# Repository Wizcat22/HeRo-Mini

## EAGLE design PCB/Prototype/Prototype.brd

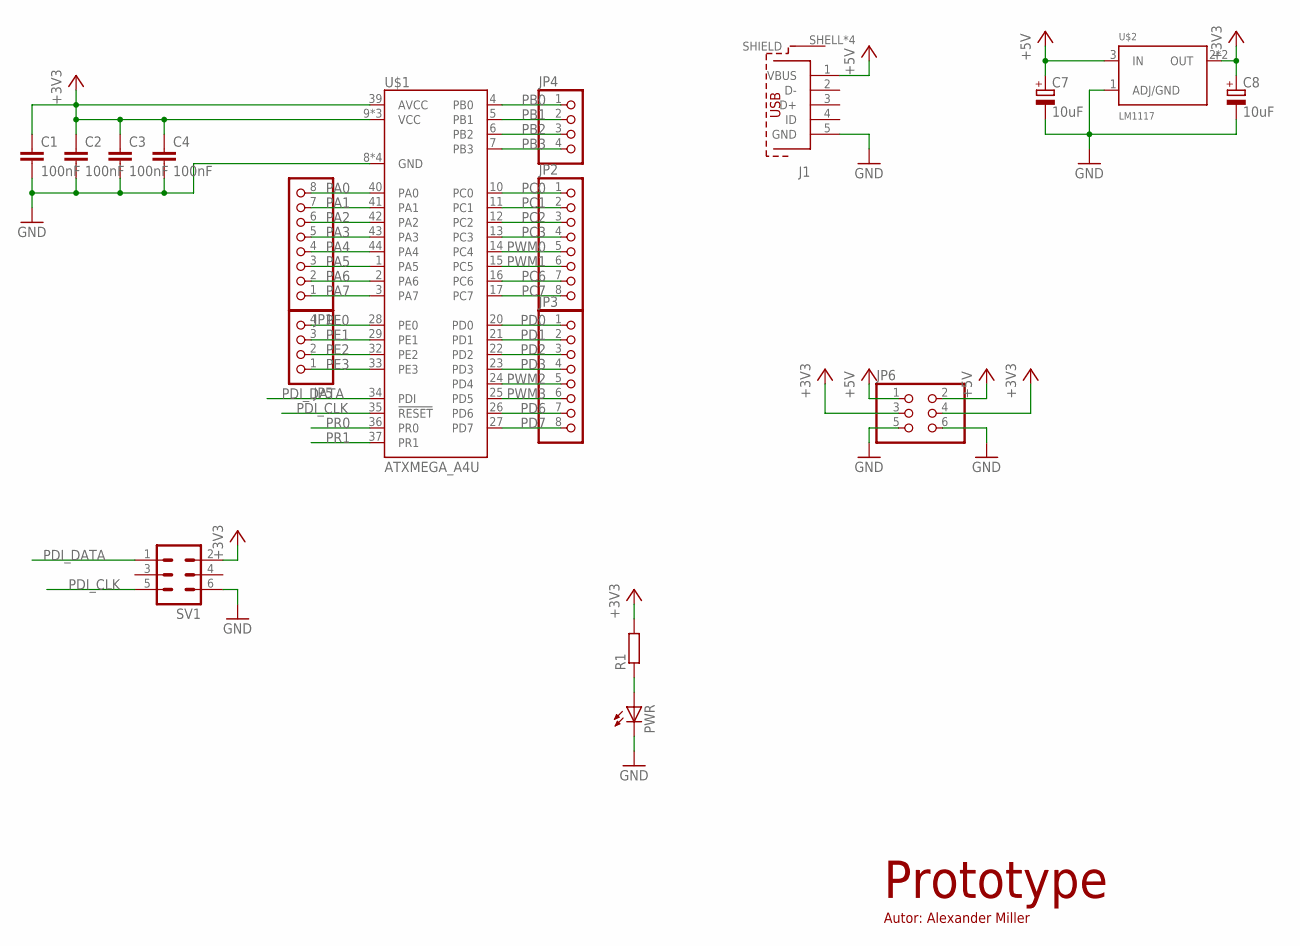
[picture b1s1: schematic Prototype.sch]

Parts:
C1, C2, C3, C4: 100nF; C0805
C7, C8: 10uF; SMC_P
J1: 629105136821
JP1, JP2, JP3: PINHD-1X8; 1X08
JP4, JP5: PINHD-1X4; 1X04
JP6: PINHD-2X3; 2X03
PWR: LEDSML0805; SML0805
R1: R-EU_R0805; R0805
SV1: ML6
U$1: ATXMEGA_A4U; QFP80P1200X1200X120-44
U$2: LM1117; SOT223

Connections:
+3V3: C1.1, C2.1, C3.1, C4.1, C8.+, JP6.3, JP6.4, R1.2, SV1.2, U$1.9 (VCC), U$1.19 (VCC), U$1.31 (VCC), U$1.39 (AVCC), U$2.2 (OUT), U$2.4 (OUT)
+5V: C7.+, J1.1 (VBUS), JP6.1, JP6.2, U$2.3 (IN)
GND: C1.2, C2.2, C3.2, C4.2, C7.-, C8.-, J1.5 (GND), JP6.5, JP6.6, PWR.C, SV1.6, U$1.8 (GND), U$1.18 (GND), U$1.30 (GND), U$1.38 (GND), U$2.1 (ADJ/GND)
unnamed: PWR.A, R1.1
PA0: JP1.8, U$1.40 (PA0)
PA1: JP1.7, U$1.41 (PA1)
PA2: JP1.6, U$1.42 (PA2)
PA3: JP1.5, U$1.43 (PA3)
PA4: JP1.4, U$1.44 (PA4)
PA5: JP1.3, U$1.1 (PA5)
PA6: JP1.2, U$1.2 (PA6)
PA7: JP1.1, U$1.3 (PA7)
PB0: JP4.1, U$1.4 (PB0)
PB1: JP4.2, U$1.5 (PB1)
PB2: JP4.3, U$1.6 (PB2)
PB3: JP4.4, U$1.7 (PB3)
PC0: JP2.1, U$1.10 (PC0)
PC1: JP2.2, U$1.11 (PC1)
PC2: JP2.3, U$1.12 (PC2)
PC3: JP2.4, U$1.13 (PC3)
PC6: JP2.7, U$1.16 (PC6)
PC7: JP2.8, U$1.17 (PC7)
PD0: JP3.1, U$1.20 (PD0)
PD1: JP3.2, U$1.21 (PD1)
PD2: JP3.3, U$1.22 (PD2)
PD3: JP3.4, U$1.23 (PD3)
PD6: JP3.7, U$1.26 (PD6)
PD7: JP3.8, U$1.27 (PD7)
PDI_CLK: SV1.5, U$1.35 (!RESET)
PDI_DATA: SV1.1, U$1.34 (PDI)
PE0: JP5.4, U$1.28 (PE0)
PE1: JP5.3, U$1.29 (PE1)
PE2: JP5.2, U$1.32 (PE2)
PE3: JP5.1, U$1.33 (PE3)
PR0: U$1.36 (PR0)
PR1: U$1.37 (PR1)
PWM0: JP2.5, U$1.14 (PC4)
PWM1: JP2.6, U$1.15 (PC5)
PWM2: JP3.5, U$1.24 (PD4)
PWM3: JP3.6, U$1.25 (PD5)

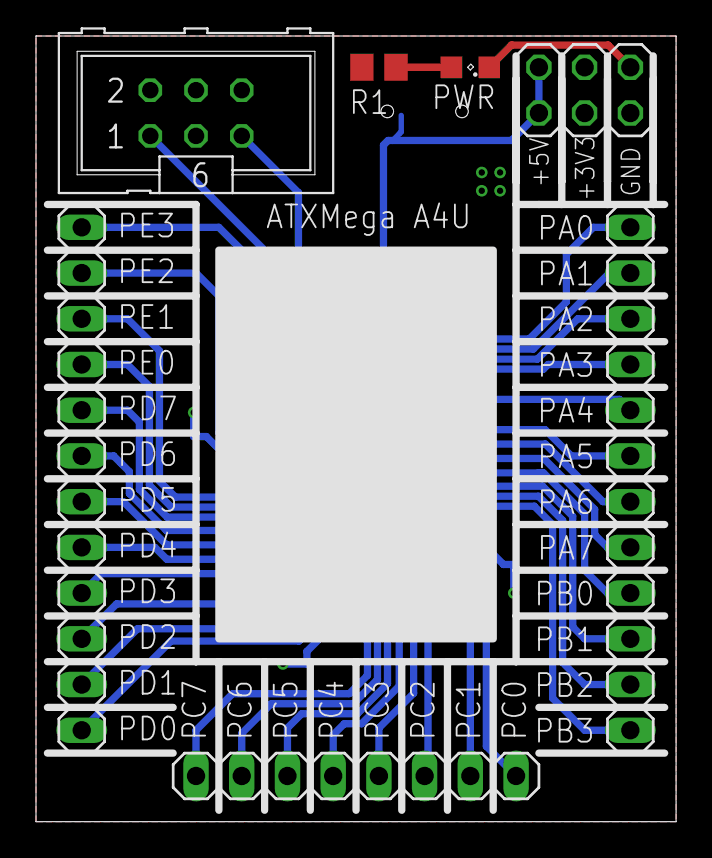
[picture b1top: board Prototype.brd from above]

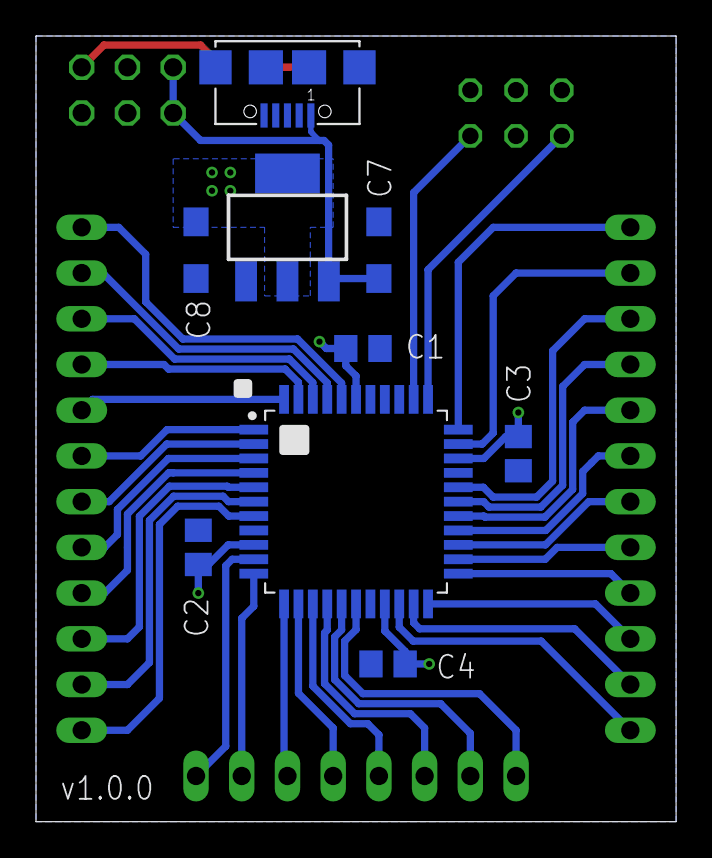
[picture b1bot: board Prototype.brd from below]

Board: 2 copper layers, 35.6 x 43.6 mm, 18 parts (9 on the bottom side), 38 nets.

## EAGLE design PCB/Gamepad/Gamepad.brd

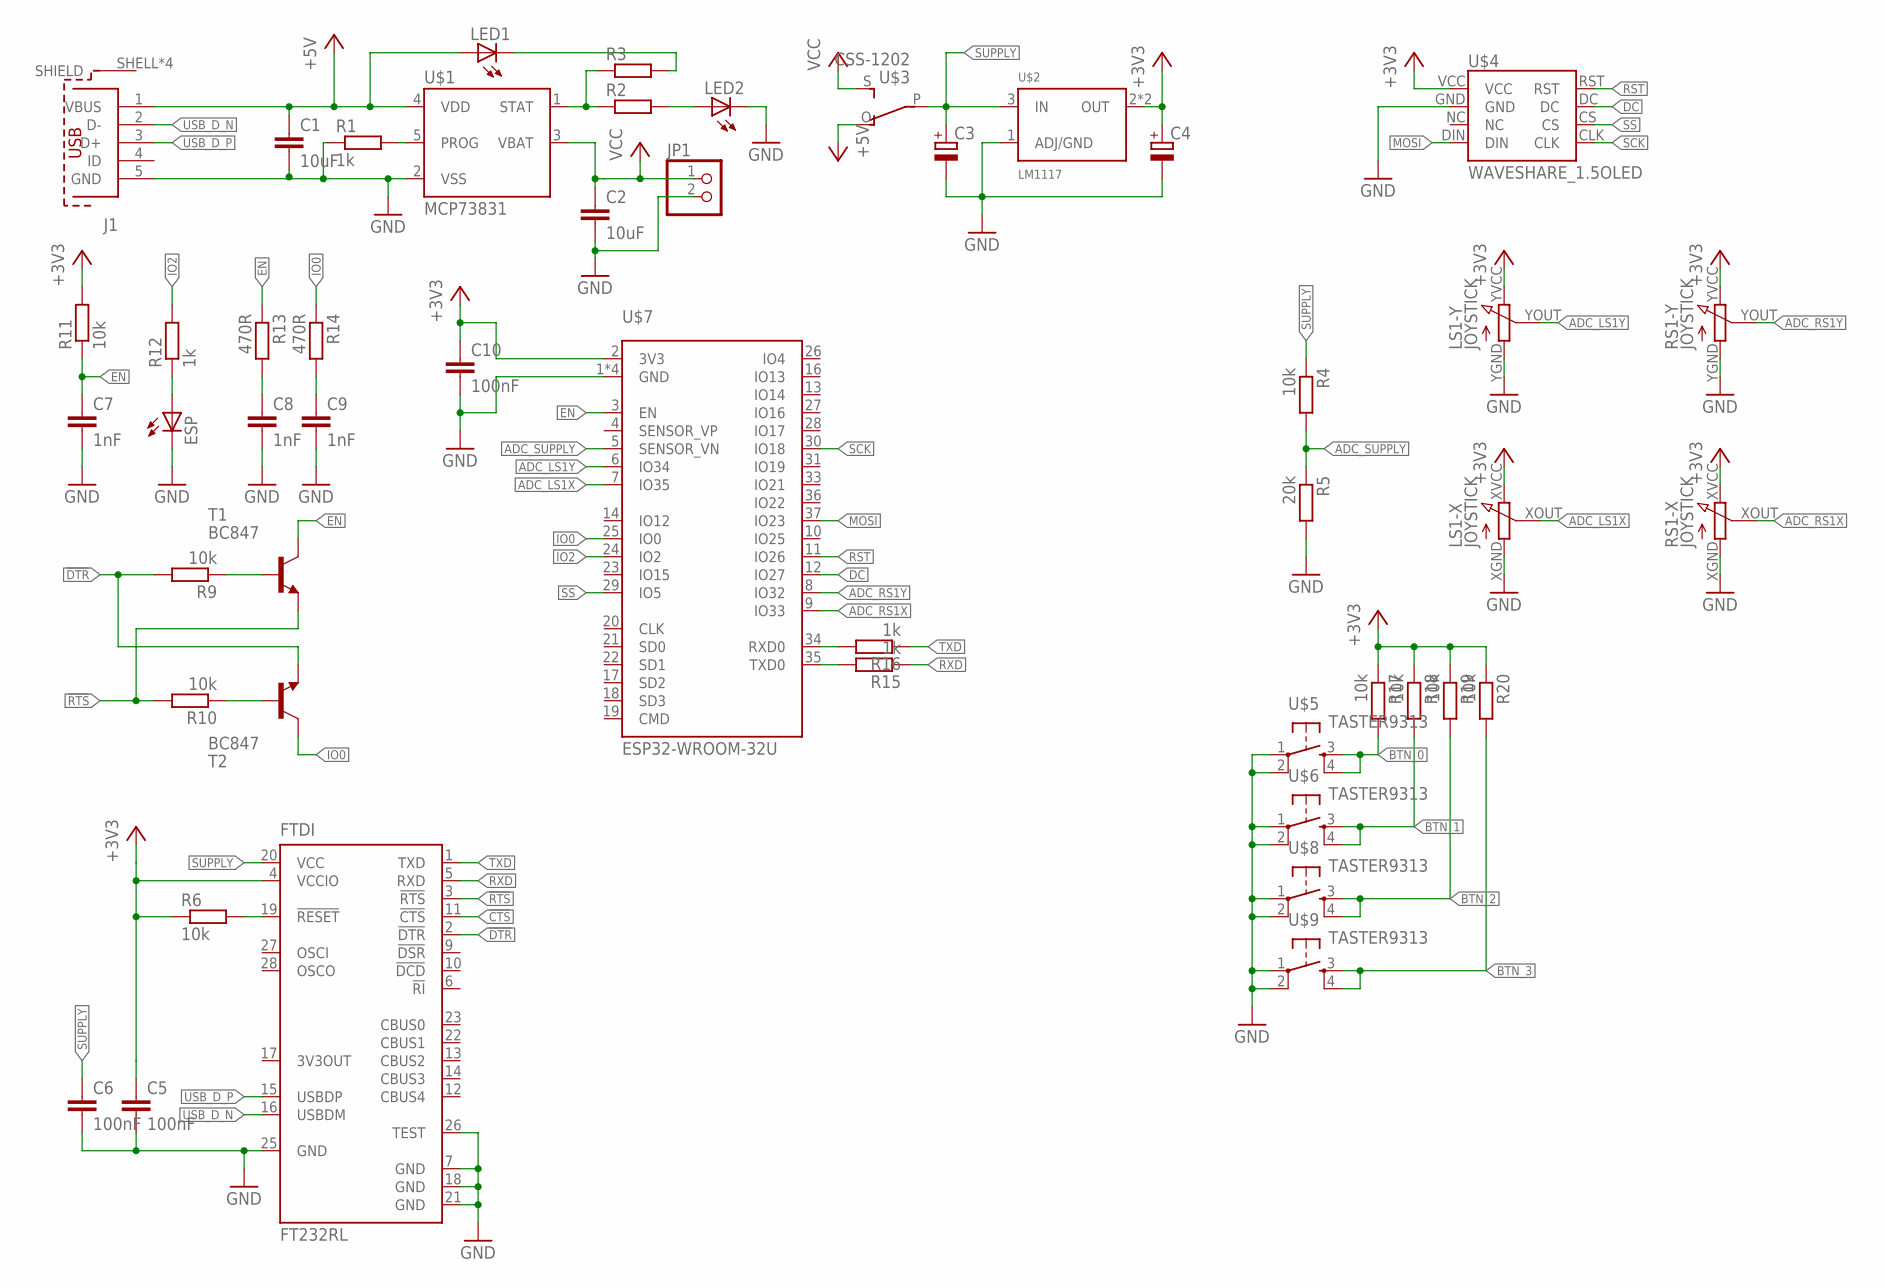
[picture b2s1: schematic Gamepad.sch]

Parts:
C1, C2: 10uF; C0805
C3, C4: CPOL-EUSMCP; SMC_P
C5, C6, C10: 100nF; C0805
C7, C8, C9: 1nF; C0805
ESP: LEDCHIP-LED0805; CHIP-LED0805
FTDI: FT232RL; SSOP28
J1: 629105136821
JP1: PINHD-1X2; 1X02
LED1, LED2: LED3MM
LS1: JOYSTICK
R1, R12, R15, R16: 1k; R0805
R2, R3: R-EU_R0805; R0805
R4, R6, R9, R10, R11, R17, R18, R19, R20: 10k; R0805
R5: 20k; R0805
R13, R14: 470R; R0805
RS1: JOYSTICK
T1, T2: BC847; SOT23
U$1: MCP73831; SOT95P280X145-5
U$2: LM1117; SOT223
U$3: CSS-1202
U$4: WAVESHARE_1.5OLED
U$5, U$6, U$8, U$9: TASTER9313
U$7: ESP32-WROOM-32U

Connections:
!CTS: FTDI.11 (!CTS)
!DTR: FTDI.2 (!DTR), R9.2, T2.2 (E)
!RTS: FTDI.3 (!RTS), R10.2, T1.2 (E)
+3V3: C4.+, C5.1, C10.1, FTDI.4 (VCCIO), LS1.XVCC (VCC), LS1.YVCC (VCC), R6.1, R11.2, R17.1, R18.1, R19.1, R20.1, RS1.XVCC (VCC), RS1.YVCC (VCC), U$2.2 (OUT), U$2.4 (OUT), U$4.VCC, U$7.2 (3V3)
+5V: C1.1, J1.1 (VBUS), LED1.A, U$1.4 (VDD), U$3.O
ADC_LS1X: LS1.XOUT (OUT), U$7.7 (IO35)
ADC_LS1Y: LS1.YOUT (OUT), U$7.6 (IO34)
ADC_RS1X: RS1.XOUT (OUT), U$7.9 (IO33)
ADC_RS1Y: RS1.YOUT (OUT), U$7.8 (IO32)
ADC_SUPPLY: R4.2, R5.1, U$7.5 (SENSOR_VN)
BTN_0: R17.2, U$5.3 (S), U$5.4 (S1)
BTN_1: R18.2, U$6.3 (S), U$6.4 (S1)
BTN_2: R19.2, U$8.3 (S), U$8.4 (S1)
BTN_3: R20.2, U$9.3 (S), U$9.4 (S1)
DC: U$4.DC, U$7.12 (IO27)
EN: C7.1, R11.1, R13.1, T1.3 (C), U$7.3 (EN)
GND: C1.2, C2.2, C3.-, C4.-, C5.2, C6.2, C7.2, C8.2, C9.2, C10.2, ESP.C, FTDI.7 (GND), FTDI.18 (GND), FTDI.21 (GND), FTDI.25 (GND), FTDI.26 (TEST), J1.5 (GND), JP1.2, LED2.K (C), LS1.XGND (GND), LS1.YGND (GND), R1.1, R5.2, RS1.XGND (GND), RS1.YGND (GND), U$1.2 (VSS), U$2.1 (ADJ/GND), U$4.GND, U$5.1, U$5.2 (P1), U$6.1, U$6.2 (P1), U$7.1 (GND), U$7.15 (GND), U$7.38 (GND), U$7.39 (GND), U$8.1, U$8.2 (P1), U$9.1, U$9.2 (P1)
IO0: R14.1, T2.3 (C), U$7.25 (IO0)
IO2: R12.2, U$7.24 (IO2)
MOSI: U$4.DIN, U$7.37 (IO23)
unnamed: R2.1, R3.1, U$1.1 (STAT)
unnamed: FTDI.19 (!RESET), R6.2
unnamed: R1.2, U$1.5 (PROG)
unnamed: LED1.K (C), R3.2
unnamed: LED2.A, R2.2
unnamed: R9.1, T1.1 (B)
unnamed: R10.1, T2.1 (B)
unnamed: ESP.A, R12.1
unnamed: C8.1, R13.2
unnamed: C9.1, R14.2
unnamed: R16.2, U$7.34 (RXD0)
unnamed: R15.2, U$7.35 (TXD0)
RST: U$4.RST, U$7.11 (IO26)
RXD: FTDI.5 (RXD), R15.1
SCK: U$4.CLK, U$7.30 (IO18)
SS: U$4.CS, U$7.29 (IO5)
SUPPLY: C3.+, C6.1, FTDI.20 (VCC), R4.1, U$2.3 (IN), U$3.P
TXD: FTDI.1 (TXD), R16.1
USB_D_N: FTDI.16 (USBDM), J1.2 (D-)
USB_D_P: FTDI.15 (USBDP), J1.3 (D+)
VCC: C2.1, JP1.1, U$1.3 (VBAT), U$3.S

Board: 2 copper layers, 47 parts (31 on the bottom side), 40 nets, no tracks yet.

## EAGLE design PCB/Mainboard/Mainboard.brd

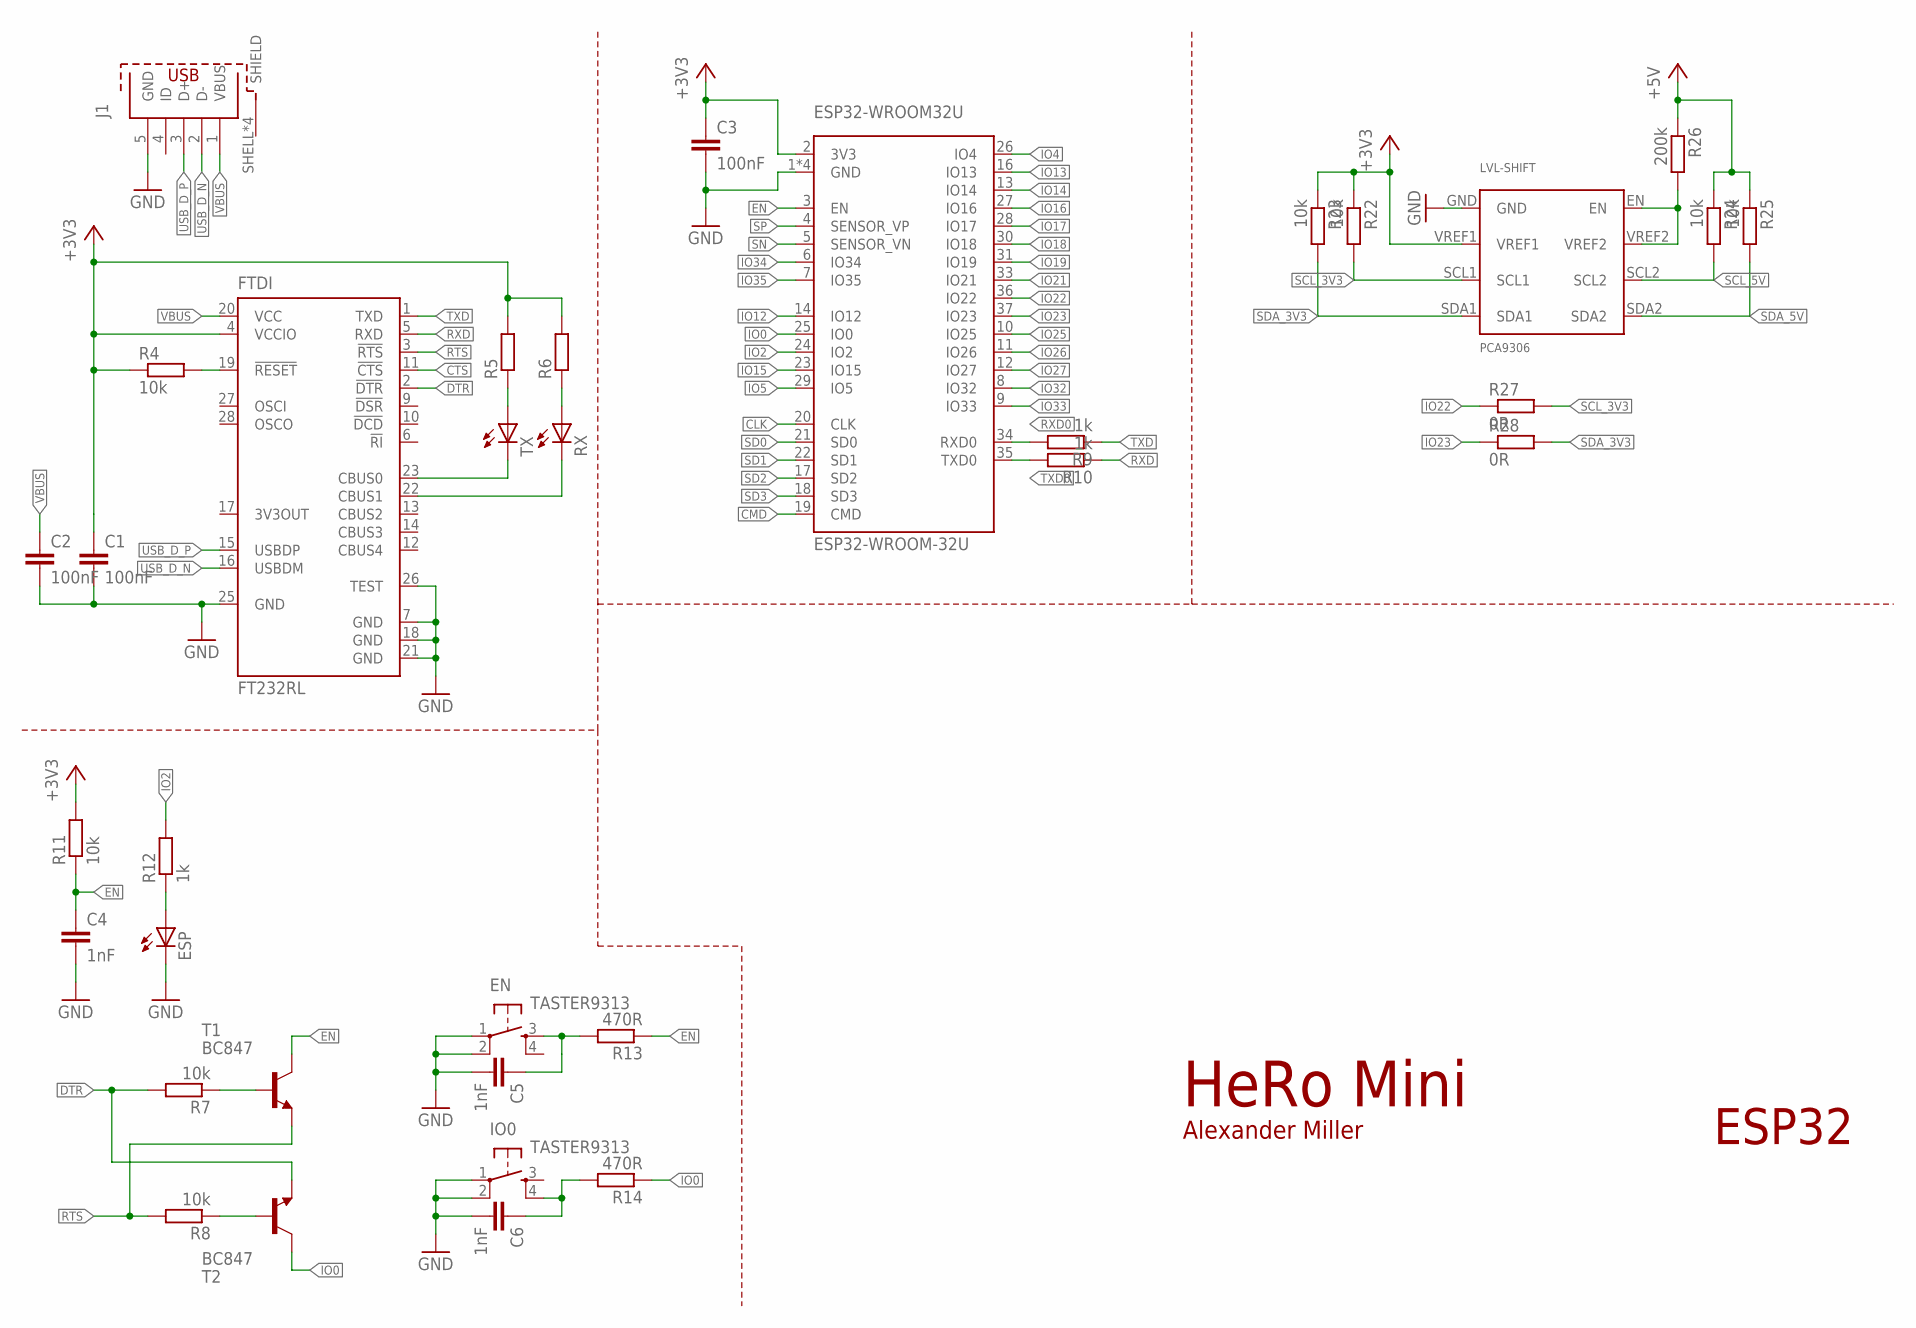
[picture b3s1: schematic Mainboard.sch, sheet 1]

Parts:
C1, C2, C3: 100nF; C0805
C4, C5, C6: 1nF; C0805
EN: TASTER9313
ESP: LEDCHIP-LED0805; CHIP-LED0805
ESP32-WROOM32U: ESP32-WROOM-32U
FTDI: FT232RL; SSOP28
IO0: TASTER9313
J1: 629105136821
LVL-SHIFT: PCA9306
R4, R7, R8, R11, R22, R23, R24, R25: 10k; R0805
R5, R6: R-EU_R0805; R0805
R9, R10, R12: 1k; R0805
R13, R14: 470R; R0805
R26: 200k; R0805
R27, R28: 0R; R0805
RX: LEDCHIP-LED0805; CHIP-LED0805
T1, T2: BC847; SOT23
TX: LEDCHIP-LED0805; CHIP-LED0805

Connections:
!CTS: FTDI.11 (!CTS)
!DTR: FTDI.2 (!DTR), R7.2, T2.2 (E)
!RTS: FTDI.3 (!RTS), R8.2, T1.2 (E)
+3V3: C1.1, C3.1, ESP32-WROOM32U.2 (3V3), FTDI.4 (VCCIO), LVL-SHIFT.VREF1, R4.1, R5.2, R6.2, R11.2, R22.1, R23.1; also elsewhere on the board
+5V: R24.1, R25.1, R26.1; also elsewhere on the board
CLK: ESP32-WROOM32U.20 (CLK)
CMD: ESP32-WROOM32U.19 (CMD)
EN: C4.1, ESP32-WROOM32U.3 (EN), R11.1, R13.1, T1.3 (C)
GND: C1.2, C2.2, C3.2, C4.2, C5.2, C6.2, EN.1, EN.2 (P1), ESP.C, ESP32-WROOM32U.1 (GND), ESP32-WROOM32U.15 (GND), ESP32-WROOM32U.38 (GND), ESP32-WROOM32U.39 (GND), FTDI.7 (GND), FTDI.18 (GND), FTDI.21 (GND), FTDI.25 (GND), FTDI.26 (TEST), IO0.1, IO0.2 (P1), J1.5 (GND), LVL-SHIFT.GND; also elsewhere on the board
IO0: ESP32-WROOM32U.25 (IO0), R14.1, T2.3 (C)
IO2: ESP32-WROOM32U.24 (IO2), R12.2
IO4: ESP32-WROOM32U.26 (IO4)
IO5: ESP32-WROOM32U.29 (IO5)
IO12: ESP32-WROOM32U.14 (IO12)
IO13: ESP32-WROOM32U.16 (IO13)
IO14: ESP32-WROOM32U.13 (IO14)
IO15: ESP32-WROOM32U.23 (IO15)
IO16: ESP32-WROOM32U.27 (IO16)
IO17: ESP32-WROOM32U.28 (IO17)
IO18: ESP32-WROOM32U.30 (IO18)
IO19: ESP32-WROOM32U.31 (IO19)
IO21: ESP32-WROOM32U.33 (IO21)
IO22: ESP32-WROOM32U.36 (IO22), R27.1
IO23: ESP32-WROOM32U.37 (IO23), R28.1
IO25: ESP32-WROOM32U.10 (IO25)
IO26: ESP32-WROOM32U.11 (IO26)
IO27: ESP32-WROOM32U.12 (IO27)
IO32: ESP32-WROOM32U.8 (IO32)
IO33: ESP32-WROOM32U.9 (IO33)
IO34: ESP32-WROOM32U.6 (IO34)
IO35: ESP32-WROOM32U.7 (IO35)
unnamed: FTDI.19 (!RESET), R4.2
unnamed: FTDI.23 (CBUS0), TX.C
unnamed: FTDI.22 (CBUS1), RX.C
unnamed: R5.1, TX.A
unnamed: R6.1, RX.A
unnamed: R7.1, T1.1 (B)
unnamed: R8.1, T2.1 (B)
unnamed: ESP.A, R12.1
unnamed: C5.1, EN.3 (S), R13.2
unnamed: C6.1, IO0.4 (S1), R14.2
unnamed: LVL-SHIFT.EN, LVL-SHIFT.VREF2, R26.2
RXD: FTDI.5 (RXD), R10.1
RXD0: ESP32-WROOM32U.34 (RXD0), R9.2
SCL_3V3: LVL-SHIFT.SCL1, R22.2, R27.2
SCL_5V: LVL-SHIFT.SCL2, R24.2; also elsewhere on the board
SD0: ESP32-WROOM32U.21 (SD0)
SD1: ESP32-WROOM32U.22 (SD1)
SD2: ESP32-WROOM32U.17 (SD2)
SD3: ESP32-WROOM32U.18 (SD3)
SDA_3V3: LVL-SHIFT.SDA1, R23.2, R28.2
SDA_5V: LVL-SHIFT.SDA2, R25.2; also elsewhere on the board
SN: ESP32-WROOM32U.5 (SENSOR_VN)
SP: ESP32-WROOM32U.4 (SENSOR_VP)
TXD: FTDI.1 (TXD), R9.1
TXD0: ESP32-WROOM32U.35 (TXD0), R10.2
USB_D_N: FTDI.16 (USBDM), J1.2 (D-)
USB_D_P: FTDI.15 (USBDP), J1.3 (D+)
VBUS: C2.1, FTDI.20 (VCC), J1.1 (VBUS)

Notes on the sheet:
ESP32

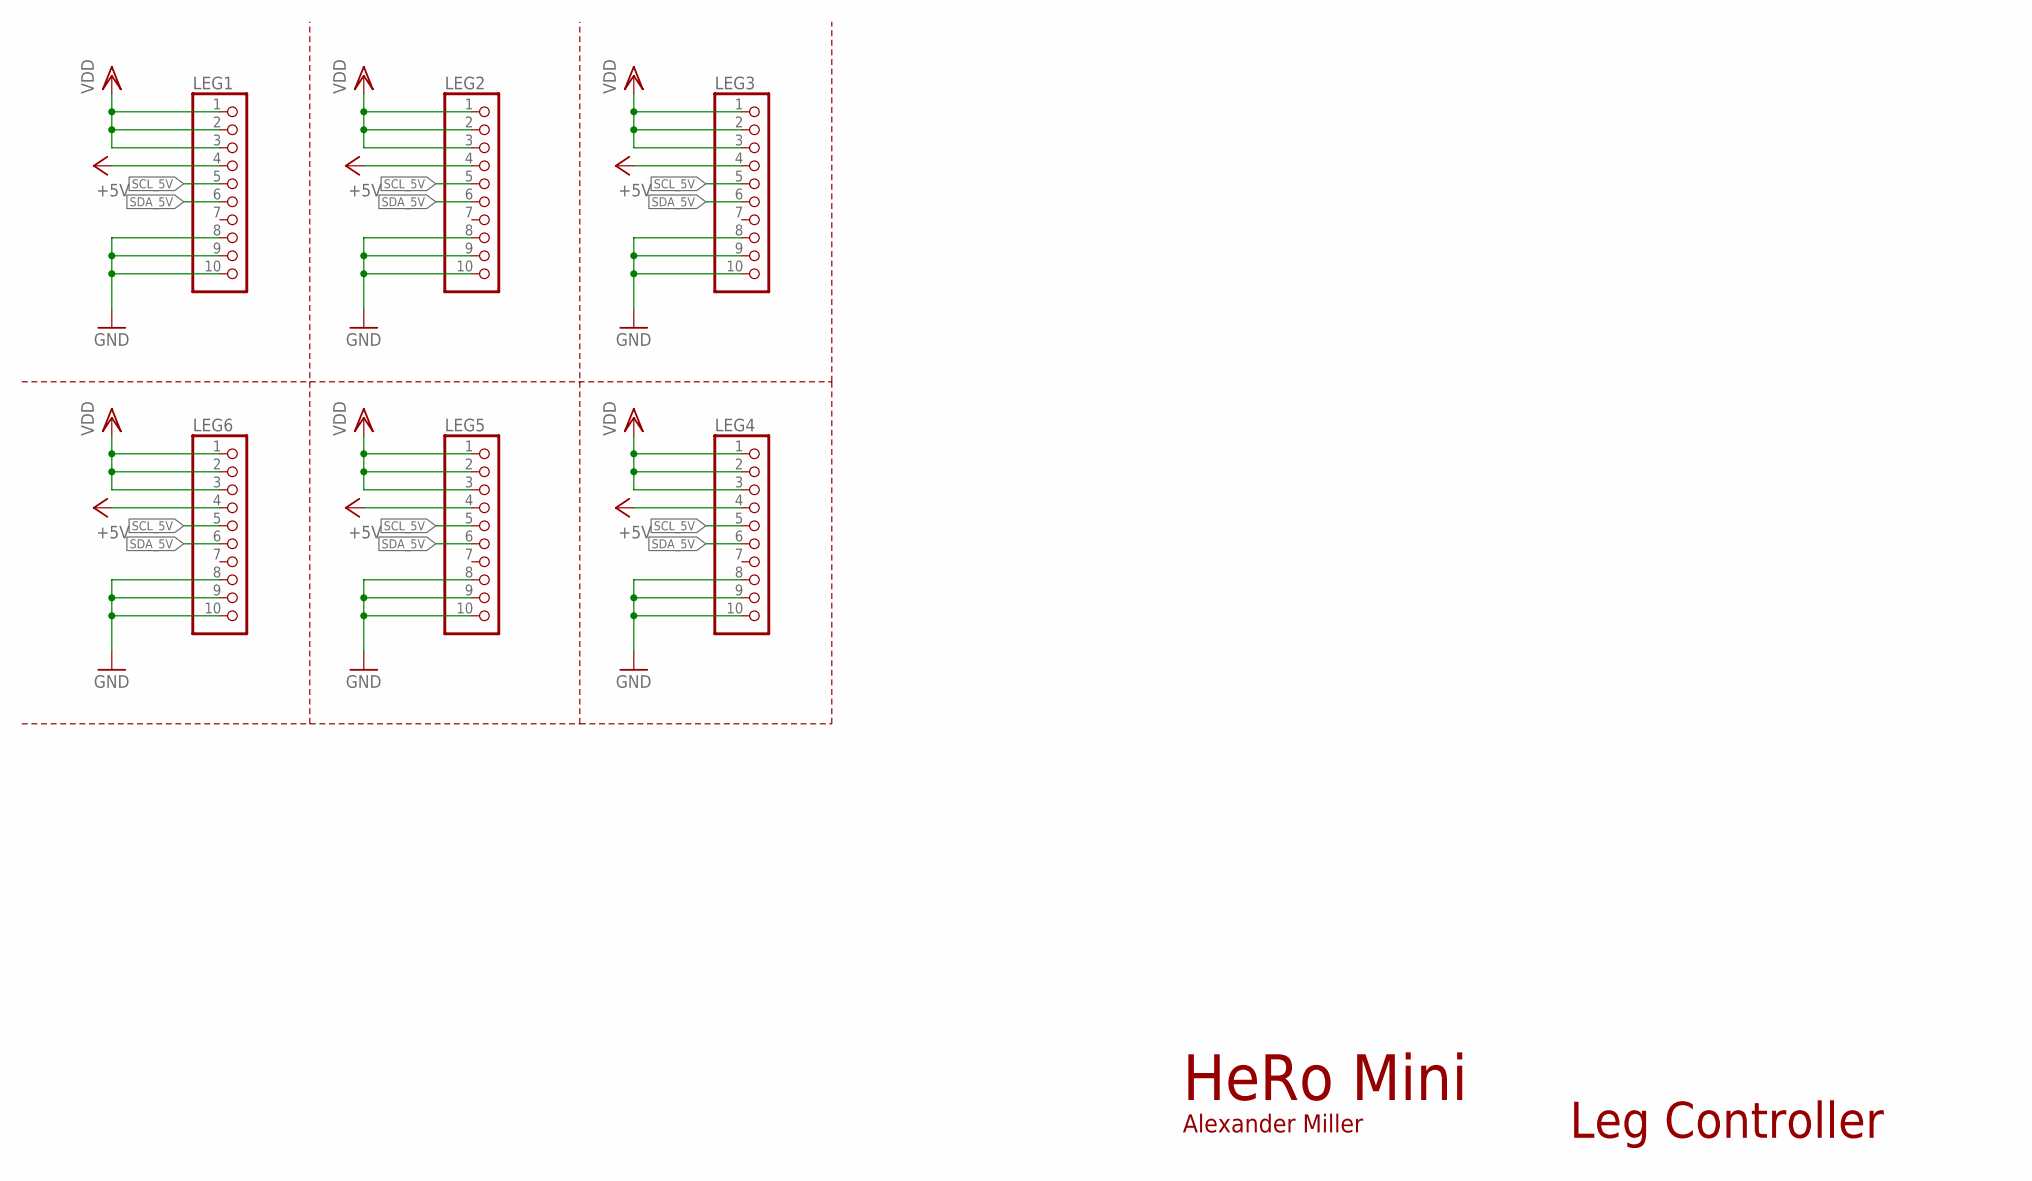
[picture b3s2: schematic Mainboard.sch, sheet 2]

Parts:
LEG1, LEG2, LEG3, LEG4, LEG5, LEG6: PINHD-1X10; 1X10

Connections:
+5V: LEG1.4, LEG2.4, LEG3.4, LEG4.4, LEG5.4, LEG6.4; also elsewhere on the board
GND: LEG1.8, LEG1.9, LEG1.10, LEG2.8, LEG2.9, LEG2.10, LEG3.8, LEG3.9, LEG3.10, LEG4.8, LEG4.9, LEG4.10, LEG5.8, LEG5.9, LEG5.10, LEG6.8, LEG6.9, LEG6.10; also elsewhere on the board
SCL_5V: LEG1.5, LEG2.5, LEG3.5, LEG4.5, LEG5.5, LEG6.5; also elsewhere on the board
SDA_5V: LEG1.6, LEG2.6, LEG3.6, LEG4.6, LEG5.6, LEG6.6; also elsewhere on the board
VDD: LEG1.1, LEG1.2, LEG1.3, LEG2.1, LEG2.2, LEG2.3, LEG3.1, LEG3.2, LEG3.3, LEG4.1, LEG4.2, LEG4.3, LEG5.1, LEG5.2, LEG5.3, LEG6.1, LEG6.2, LEG6.3; also elsewhere on the board

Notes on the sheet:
Leg Controller

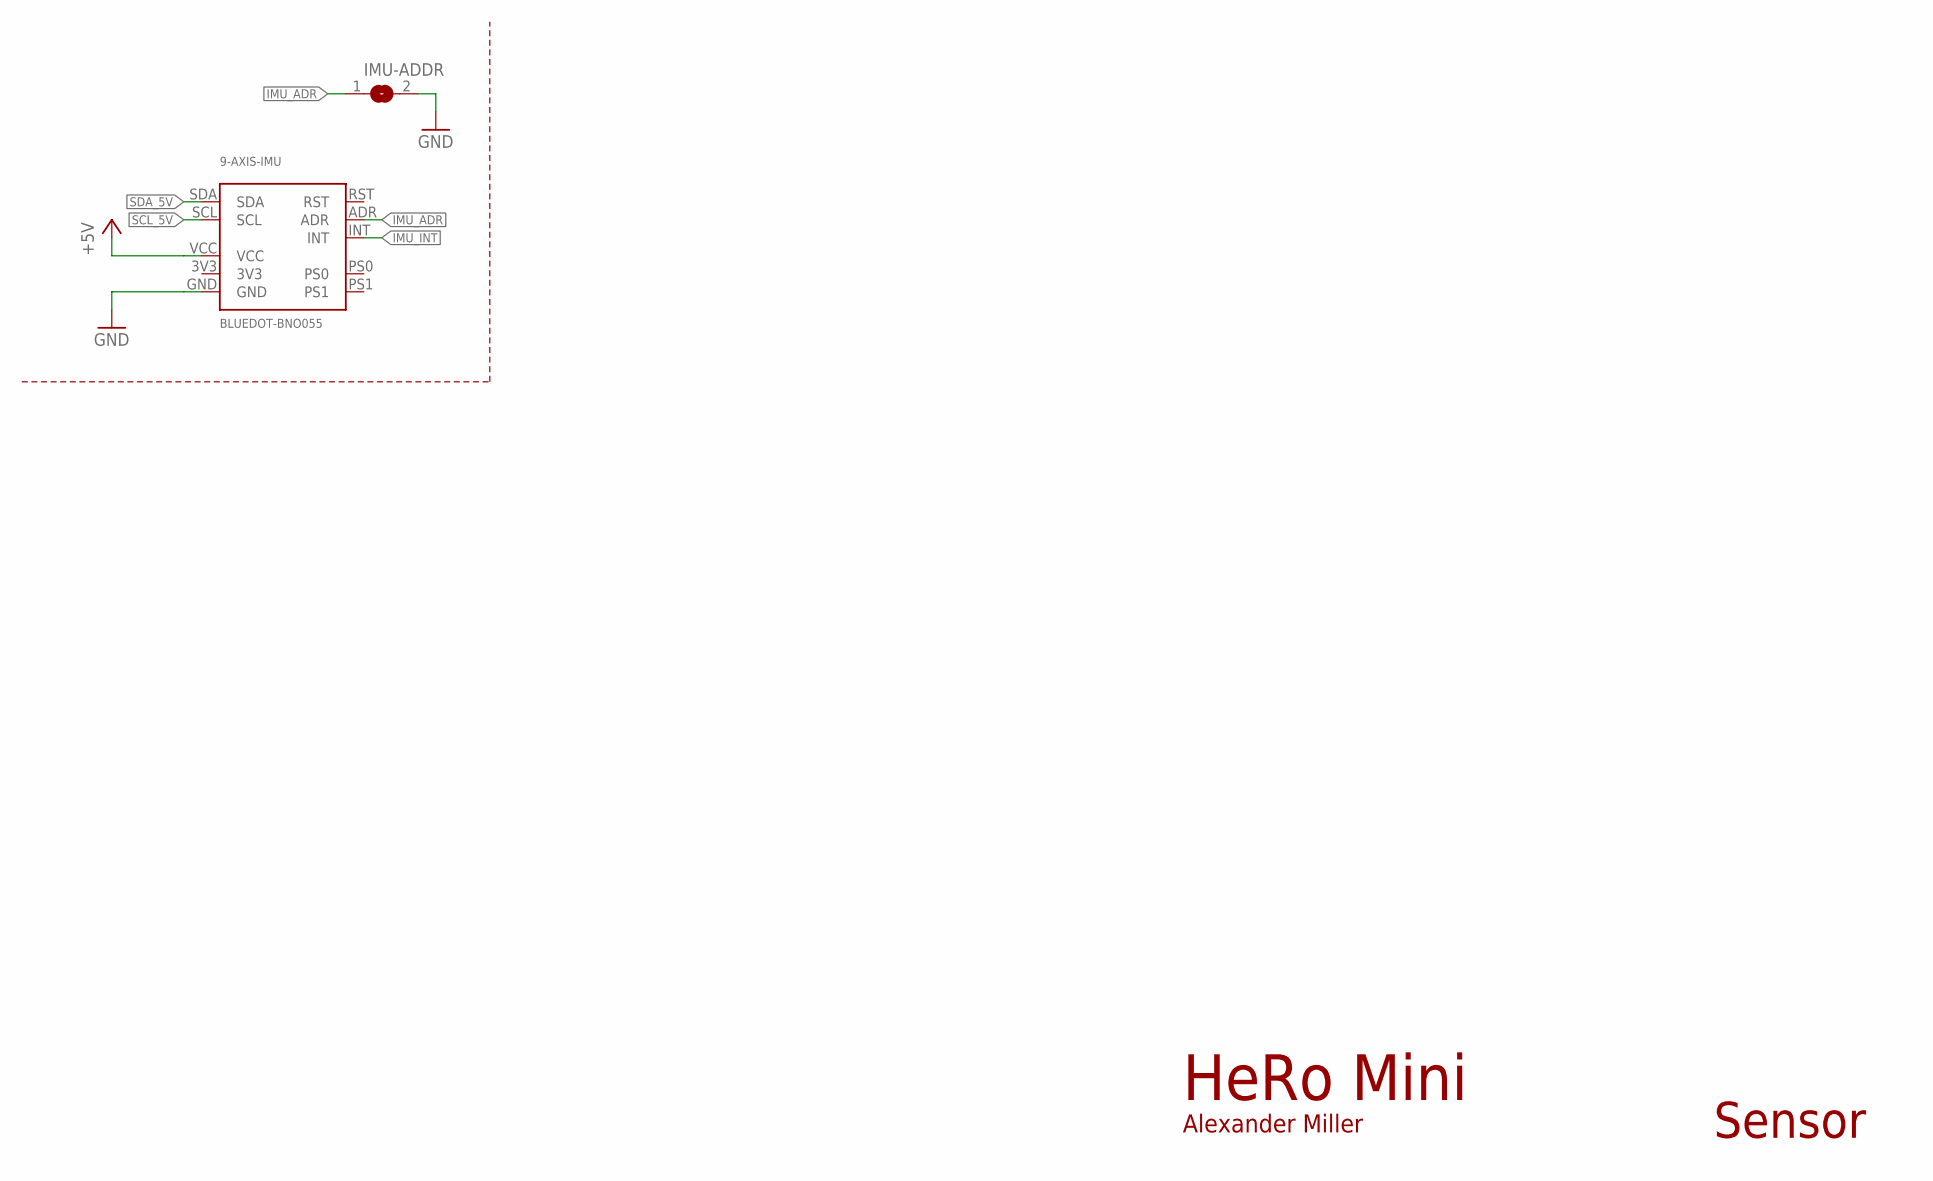
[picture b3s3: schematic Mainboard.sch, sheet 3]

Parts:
9-AXIS-IMU: BLUEDOT-BNO055
IMU-ADDR: SJ

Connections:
+5V: 9-AXIS-IMU.VCC; also elsewhere on the board
GND: 9-AXIS-IMU.GND, IMU-ADDR.2; also elsewhere on the board
IMU_ADR: 9-AXIS-IMU.ADR, IMU-ADDR.1
IMU_INT: 9-AXIS-IMU.INT
SCL_5V: 9-AXIS-IMU.SCL; also elsewhere on the board
SDA_5V: 9-AXIS-IMU.SDA; also elsewhere on the board

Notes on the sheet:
Sensor

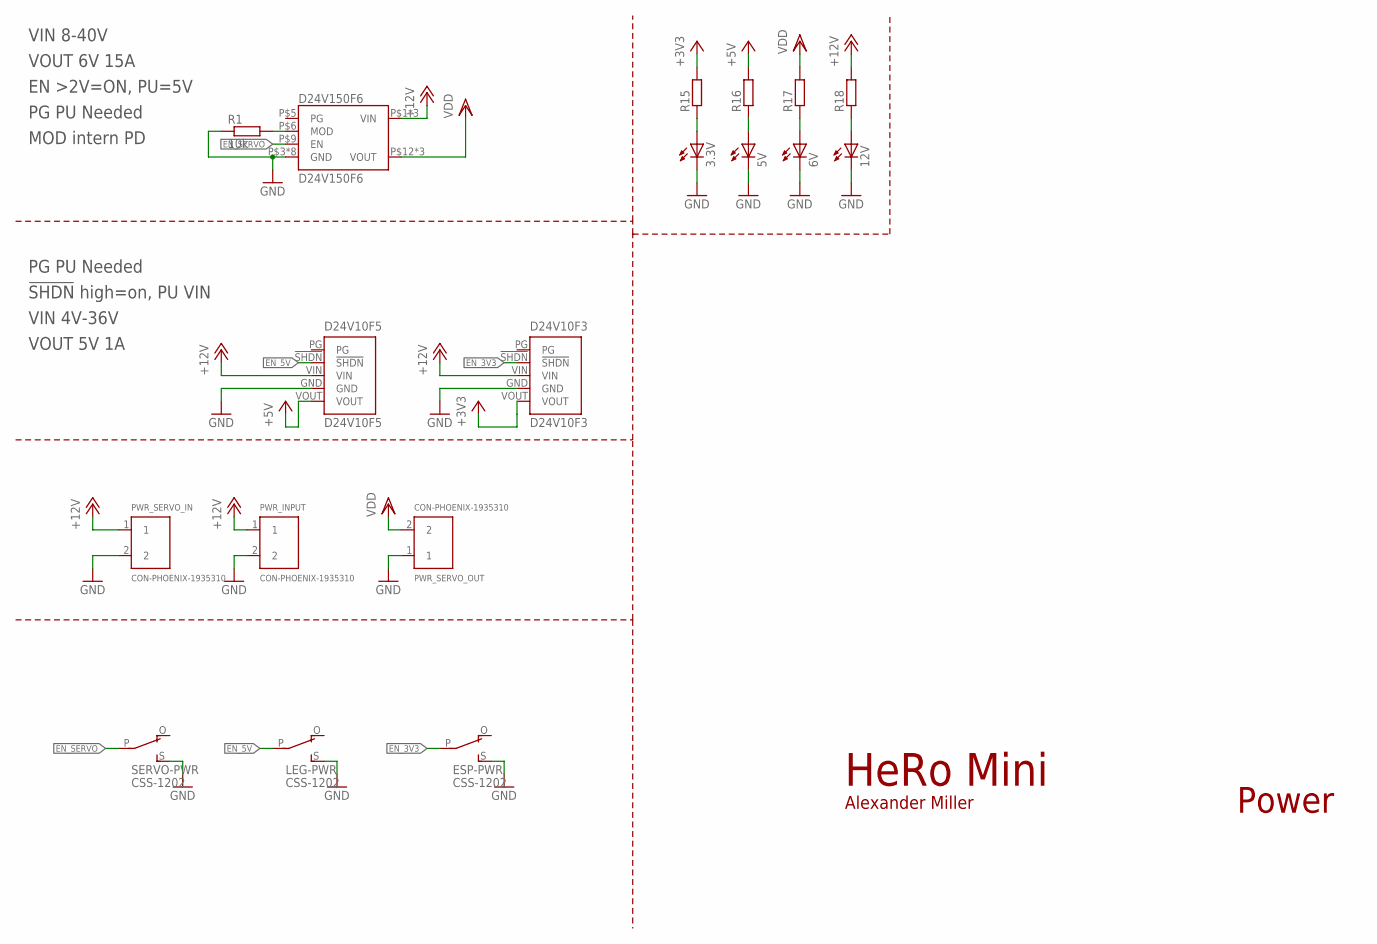
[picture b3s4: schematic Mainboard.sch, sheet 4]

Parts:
3.3V, 5V, 6V, 12V: LEDCHIP-LED0805; CHIP-LED0805
D24V10F3: D24V10F3; D24V10F5
D24V10F5: D24V10F5
D24V150F6: D24V150F6
ESP-PWR: CSS-1202
LEG-PWR: CSS-1202
PWR_INPUT: CON-PHOENIX-1935310
PWR_SERVO_IN: CON-PHOENIX-1935310
PWR_SERVO_OUT: CON-PHOENIX-1935310
R1: 10k; R0805
R15, R16, R17, R18: R-EU_R0805; R0805
SERVO-PWR: CSS-1202

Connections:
+3V3: D24V10F3.VOUT, R15.2; also elsewhere on the board
+5V: D24V10F5.VOUT, R16.2; also elsewhere on the board
+12V: D24V10F3.VIN, D24V10F5.VIN, D24V150F6.P$1 (VIN), D24V150F6.P$2 (VIN), D24V150F6.P$17 (VIN), PWR_INPUT.1, PWR_SERVO_IN.1, R18.2
EN_3V3: D24V10F3.!SHDN, ESP-PWR.P
EN_5V: D24V10F5.!SHDN, LEG-PWR.P
EN_SERVO: D24V150F6.P$9 (EN), SERVO-PWR.P
GND: 3.3V.C, 5V.C, 6V.C, 12V.C, D24V10F3.GND, D24V10F5.GND, D24V150F6.P$3 (GND), D24V150F6.P$4 (GND), D24V150F6.P$7 (GND), D24V150F6.P$8 (GND), D24V150F6.P$10 (GND), D24V150F6.P$11 (GND), D24V150F6.P$14 (GND), D24V150F6.P$16 (GND), ESP-PWR.S, LEG-PWR.S, PWR_INPUT.2, PWR_SERVO_IN.2, PWR_SERVO_OUT.1, R1.1, SERVO-PWR.S; also elsewhere on the board
unnamed: D24V150F6.P$6 (MOD), R1.2
unnamed: 5V.A, R16.1
unnamed: 6V.A, R17.1
unnamed: 3.3V.A, R15.1
unnamed: 12V.A, R18.1
VDD: D24V150F6.P$12 (VOUT), D24V150F6.P$13 (VOUT), D24V150F6.P$15 (VOUT), PWR_SERVO_OUT.2, R17.2; also elsewhere on the board

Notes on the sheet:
Power
VIN 8-40V
VOUT 6V 15A
EN >2V=ON, PU=5V
PG PU Needed
MOD intern PD
!SHDN! high=on, PU VIN
VIN 4V-36V
VOUT 5V 1A

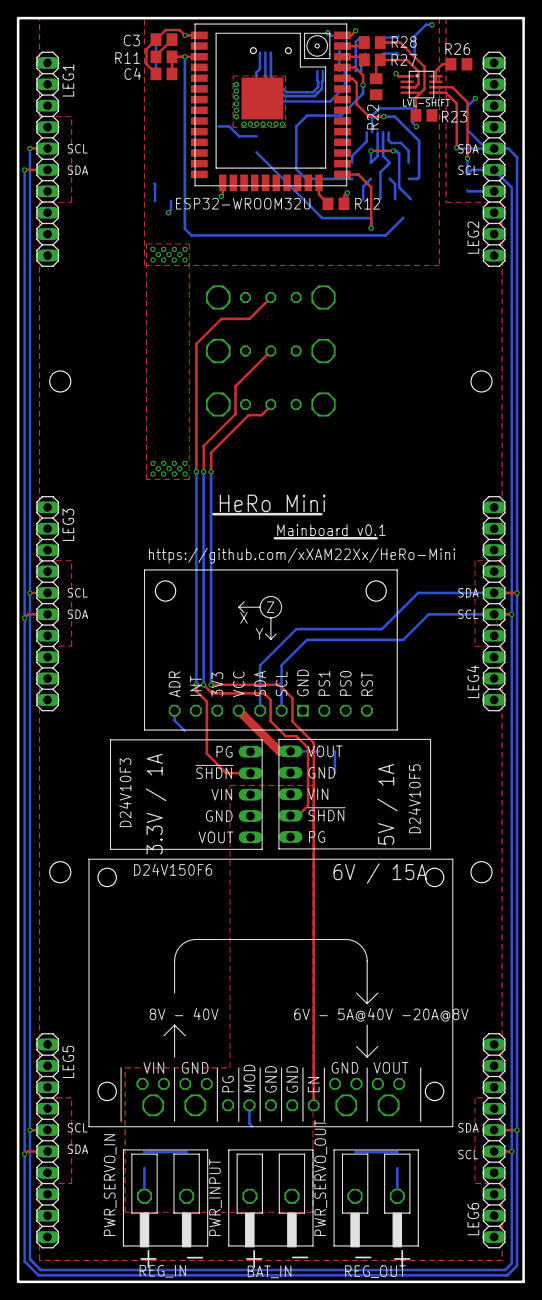
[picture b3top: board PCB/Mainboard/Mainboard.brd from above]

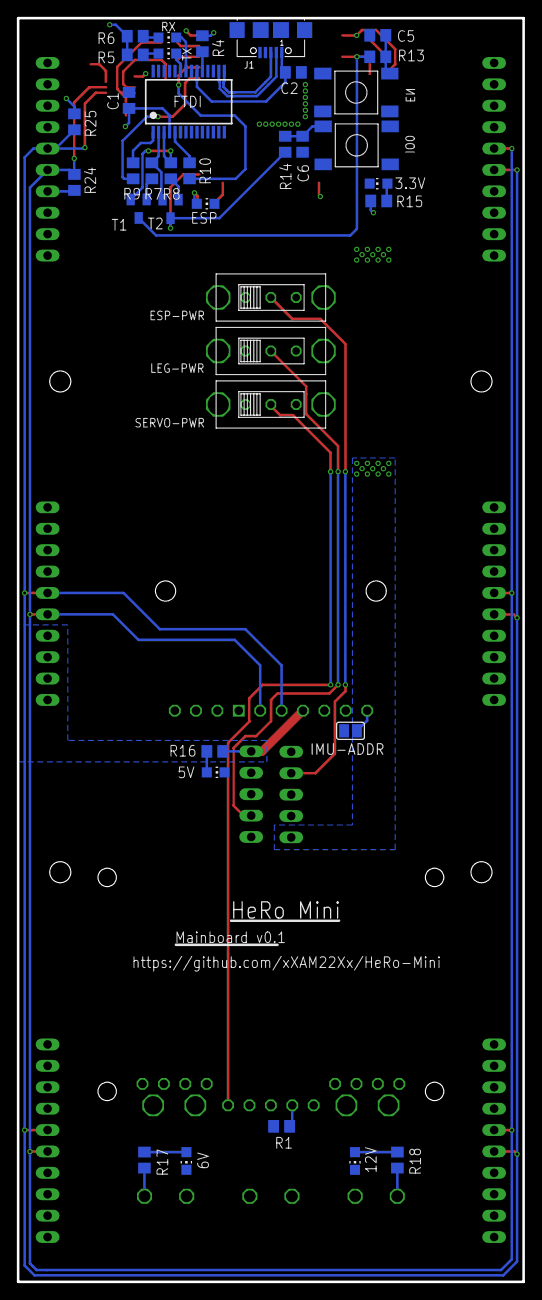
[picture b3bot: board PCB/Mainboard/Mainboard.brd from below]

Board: 2 copper layers, 60.0 x 150.0 mm, 61 parts (37 on the bottom side), 43 nets.

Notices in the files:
parts and their libraries:
InputOutputIO: Copyright: Würth Elektronik
